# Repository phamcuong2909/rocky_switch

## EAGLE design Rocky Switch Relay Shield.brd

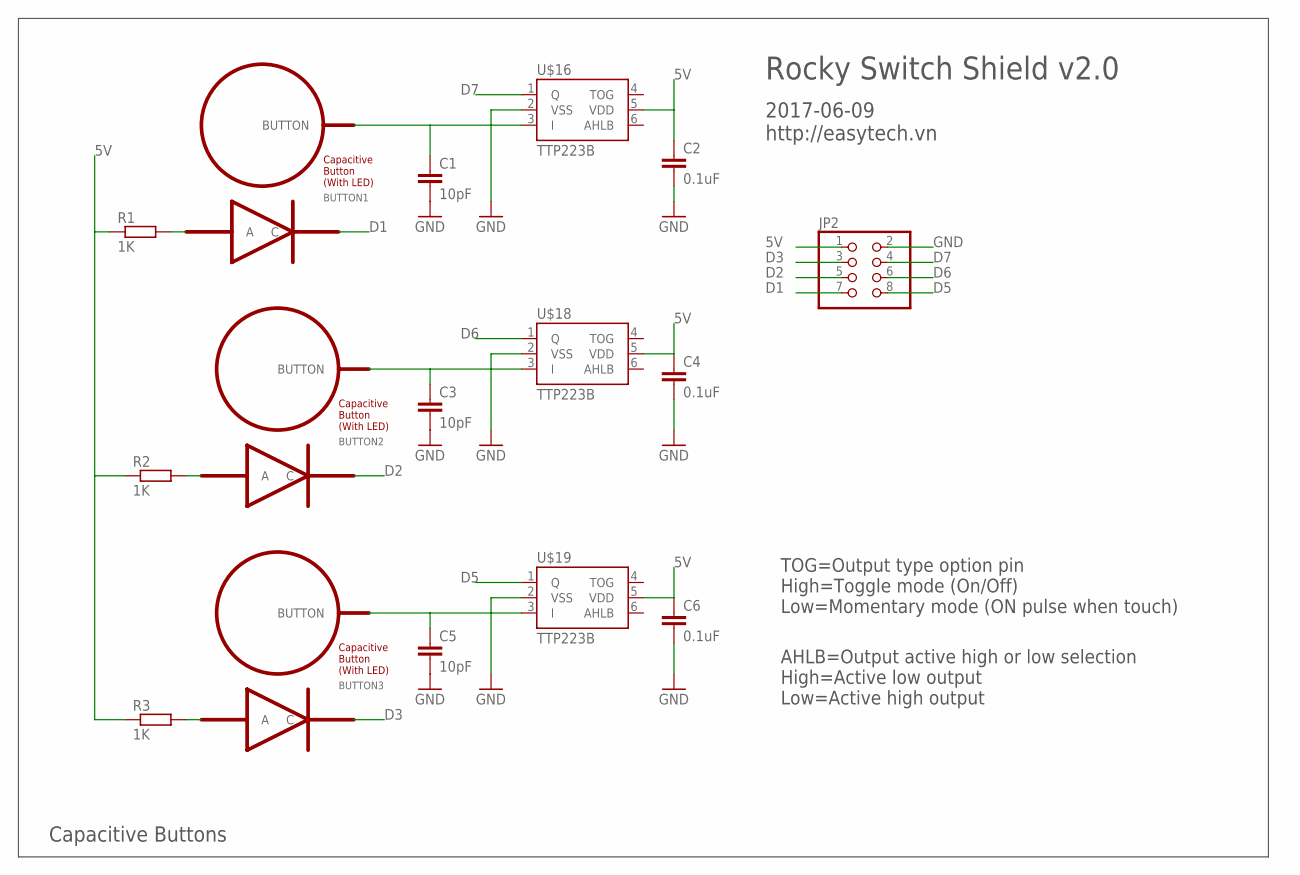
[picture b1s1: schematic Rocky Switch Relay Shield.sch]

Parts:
BUTTON1, BUTTON2, BUTTON3: BUTTON_PASSIVE_LED
C1, C3, C5: 10pF; C0805K
C2, C4, C6: 0.1uF; C0805K
JP2: PINHD-2X4; 2X04
R1, R2, R3: 1K; R0805
U$16, U$18, U$19: TTP223B; SOT23-6

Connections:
5V: C2.1, C4.1, C6.1, JP2.1, R1.1, R2.1, R3.1, U$16.5 (VDD), U$18.5 (VDD), U$19.5 (VDD)
D1: BUTTON1.C, JP2.7
D2: BUTTON2.C, JP2.5
D3: BUTTON3.C, JP2.3
D5: JP2.8, U$19.1 (Q)
D6: JP2.6, U$18.1 (Q)
D7: JP2.4, U$16.1 (Q)
GND: C1.2, C2.2, C3.2, C4.2, C5.2, C6.2, JP2.2, U$16.2 (VSS), U$18.2 (VSS), U$19.2 (VSS)
I1: BUTTON1.BUTTON, C1.1, U$16.3 (I)
I2: BUTTON2.BUTTON, C3.1, U$18.3 (I)
I3: BUTTON3.BUTTON, C5.1, U$19.3 (I)
unnamed: BUTTON1.A, R1.2
unnamed: BUTTON2.A, R2.2
unnamed: BUTTON3.A, R3.2

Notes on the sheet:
Rocky Switch Shield v2.0
2017-06-09 http://easytech.vn
Capacitive Buttons
TOG=Output type option pin High=Toggle mode (On/Off) Low=Momentary mode (ON pulse when touch)
AHLB=Output active high or low selection High=Active low output Low=Active high output

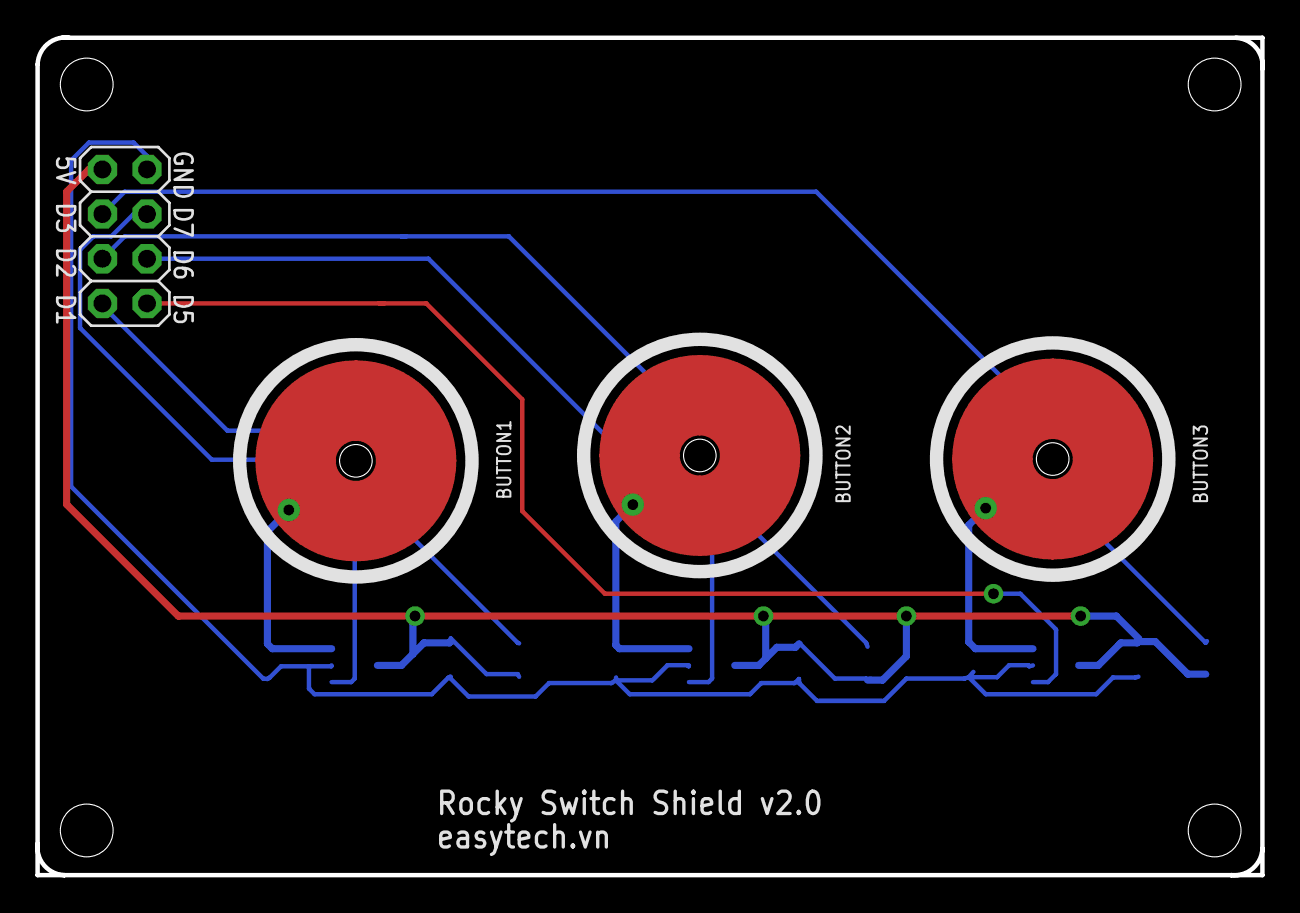
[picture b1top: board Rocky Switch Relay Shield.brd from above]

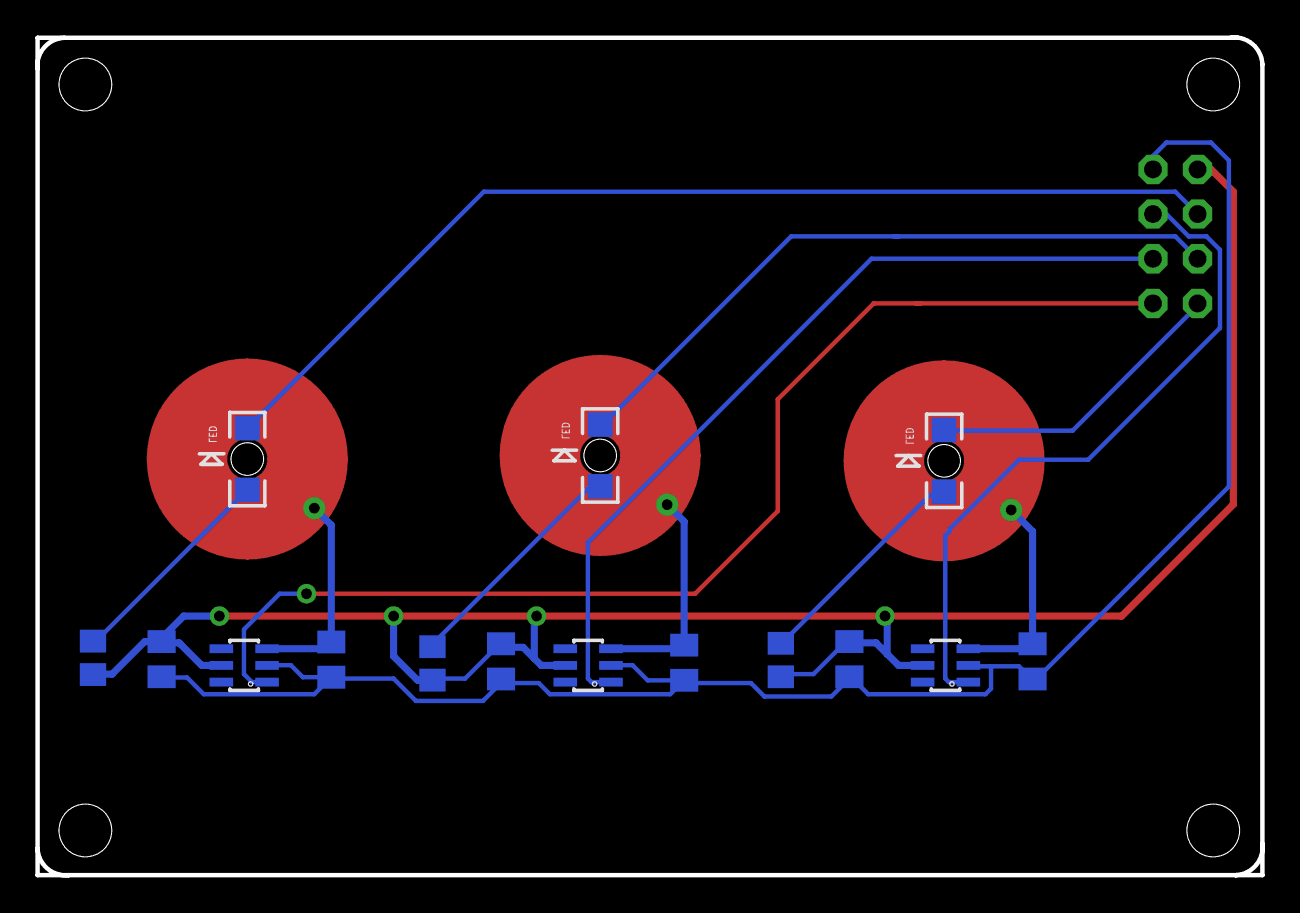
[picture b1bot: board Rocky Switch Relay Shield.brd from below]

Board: 2 copper layers, 69.7 x 47.6 mm, 20 parts (12 on the bottom side), 14 nets.

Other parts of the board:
U$6, U$7, U$8, U$9: KFH-M3

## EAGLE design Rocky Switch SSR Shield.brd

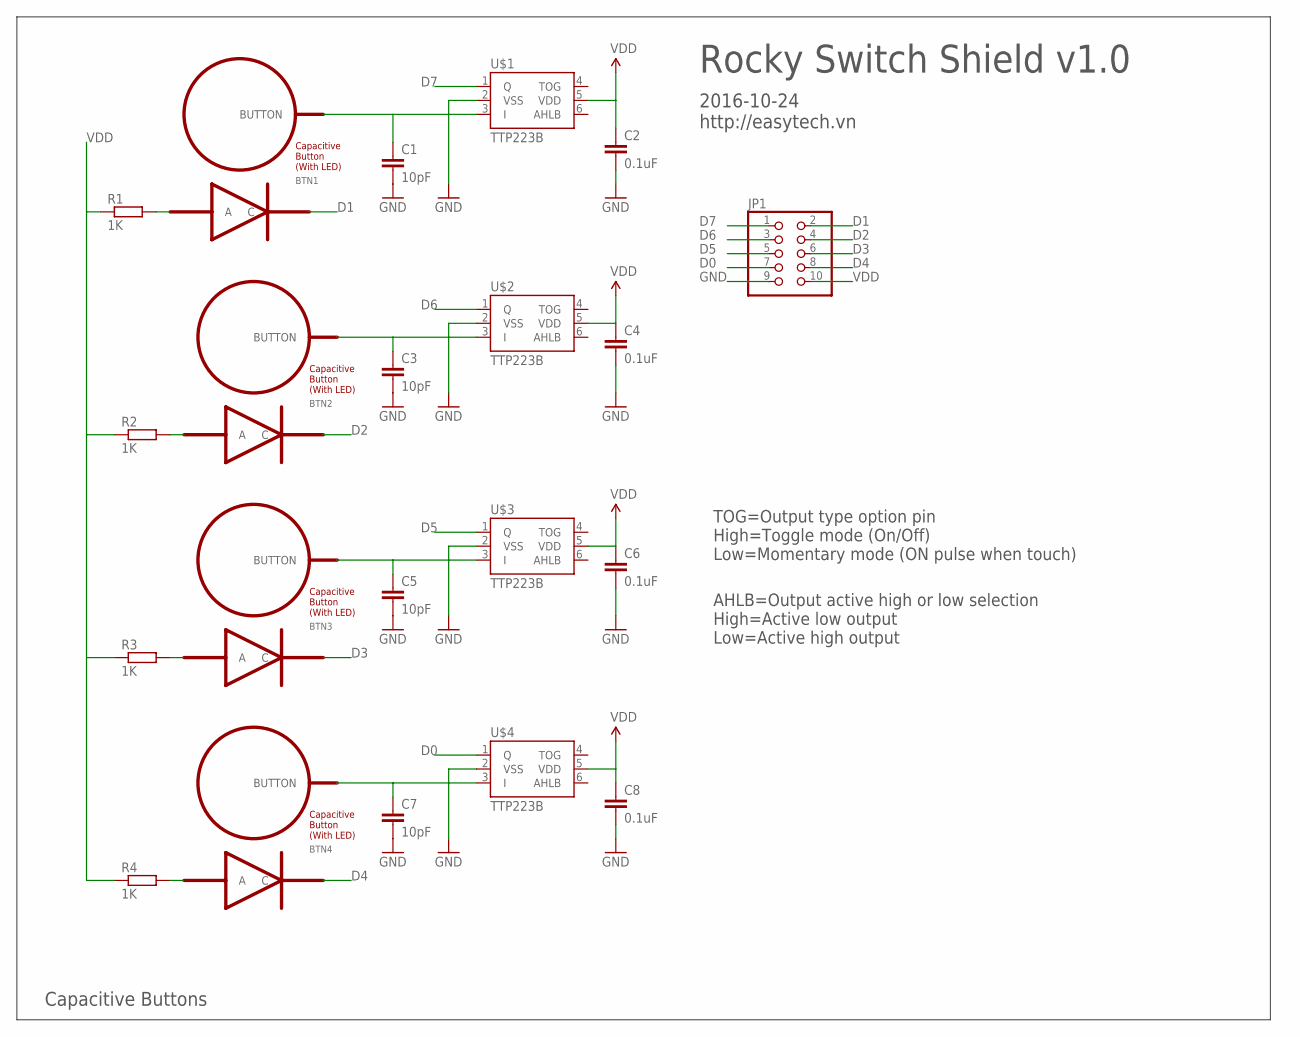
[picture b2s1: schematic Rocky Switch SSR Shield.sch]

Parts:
BTN1, BTN2, BTN3, BTN4: BUTTON_PASSIVE_LED
C1, C3, C5, C7: 10pF; C0805K
C2, C4, C6, C8: 0.1uF; C0805K
JP1: PINHD-2X5; 2X05
R1, R2, R3, R4: 1K; R0805
U$1, U$2, U$3, U$4: TTP223B; SOT23-6

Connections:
D0: JP1.7, U$4.1 (Q)
D1: BTN1.C, JP1.2
D2: BTN2.C, JP1.4
D3: BTN3.C, JP1.6
D4: BTN4.C, JP1.8
D5: JP1.5, U$3.1 (Q)
D6: JP1.3, U$2.1 (Q)
D7: JP1.1, U$1.1 (Q)
GND: C1.2, C2.2, C3.2, C4.2, C5.2, C6.2, C7.2, C8.2, JP1.9, U$1.2 (VSS), U$2.2 (VSS), U$3.2 (VSS), U$4.2 (VSS)
I1: BTN1.BUTTON, C1.1, U$1.3 (I)
I2: BTN2.BUTTON, C3.1, U$2.3 (I)
I3: BTN3.BUTTON, C5.1, U$3.3 (I)
I4: BTN4.BUTTON, C7.1, U$4.3 (I)
unnamed: BTN1.A, R1.2
unnamed: BTN2.A, R2.2
unnamed: BTN3.A, R3.2
unnamed: BTN4.A, R4.2
VDD: C2.1, C4.1, C6.1, C8.1, JP1.10, R1.1, R2.1, R3.1, R4.1, U$1.5 (VDD), U$2.5 (VDD), U$3.5 (VDD), U$4.5 (VDD)

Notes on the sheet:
Rocky Switch Shield v1.0
2016-10-24 http://easytech.vn
Capacitive Buttons
TOG=Output type option pin High=Toggle mode (On/Off) Low=Momentary mode (ON pulse when touch)
AHLB=Output active high or low selection High=Active low output Low=Active high output

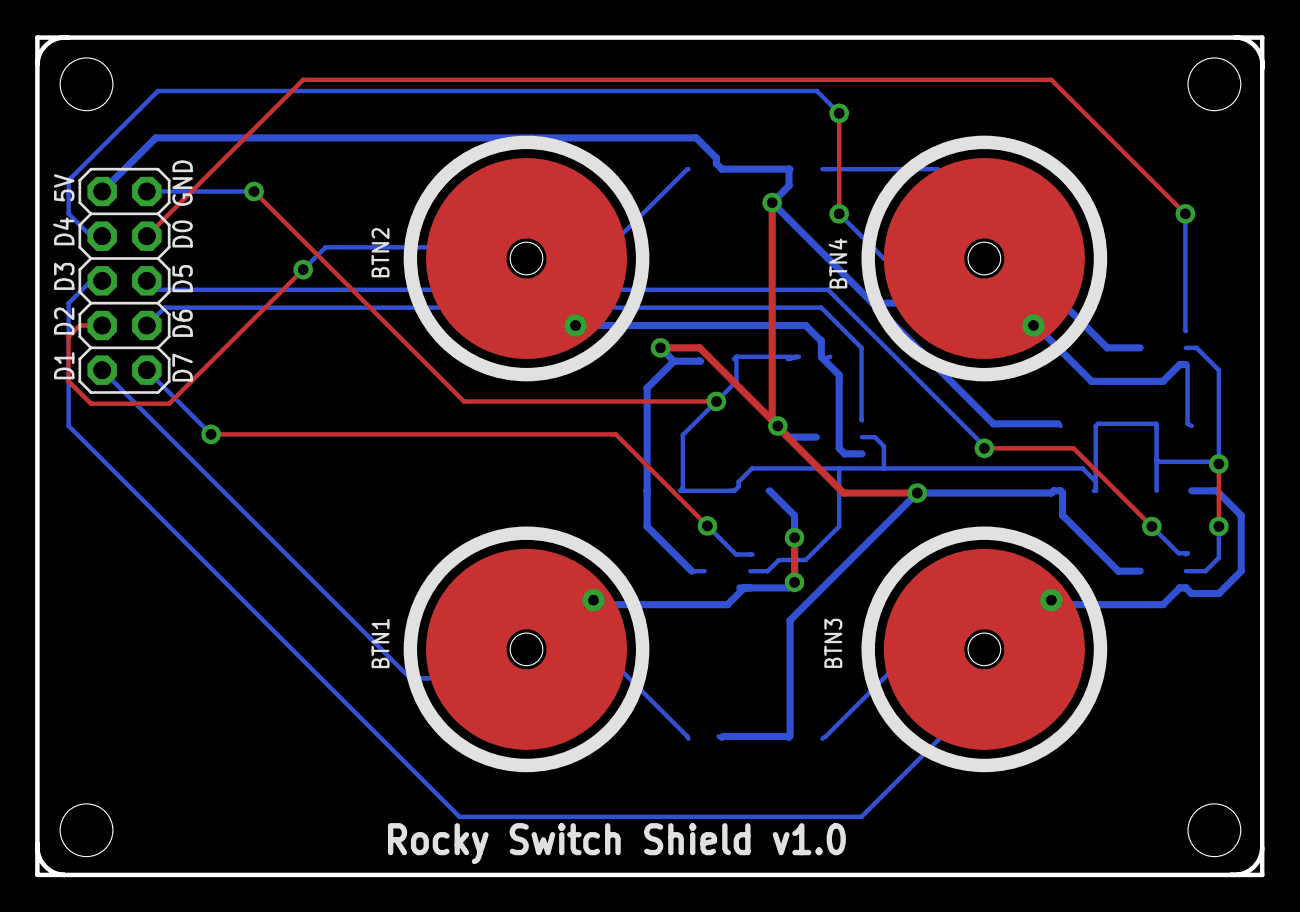
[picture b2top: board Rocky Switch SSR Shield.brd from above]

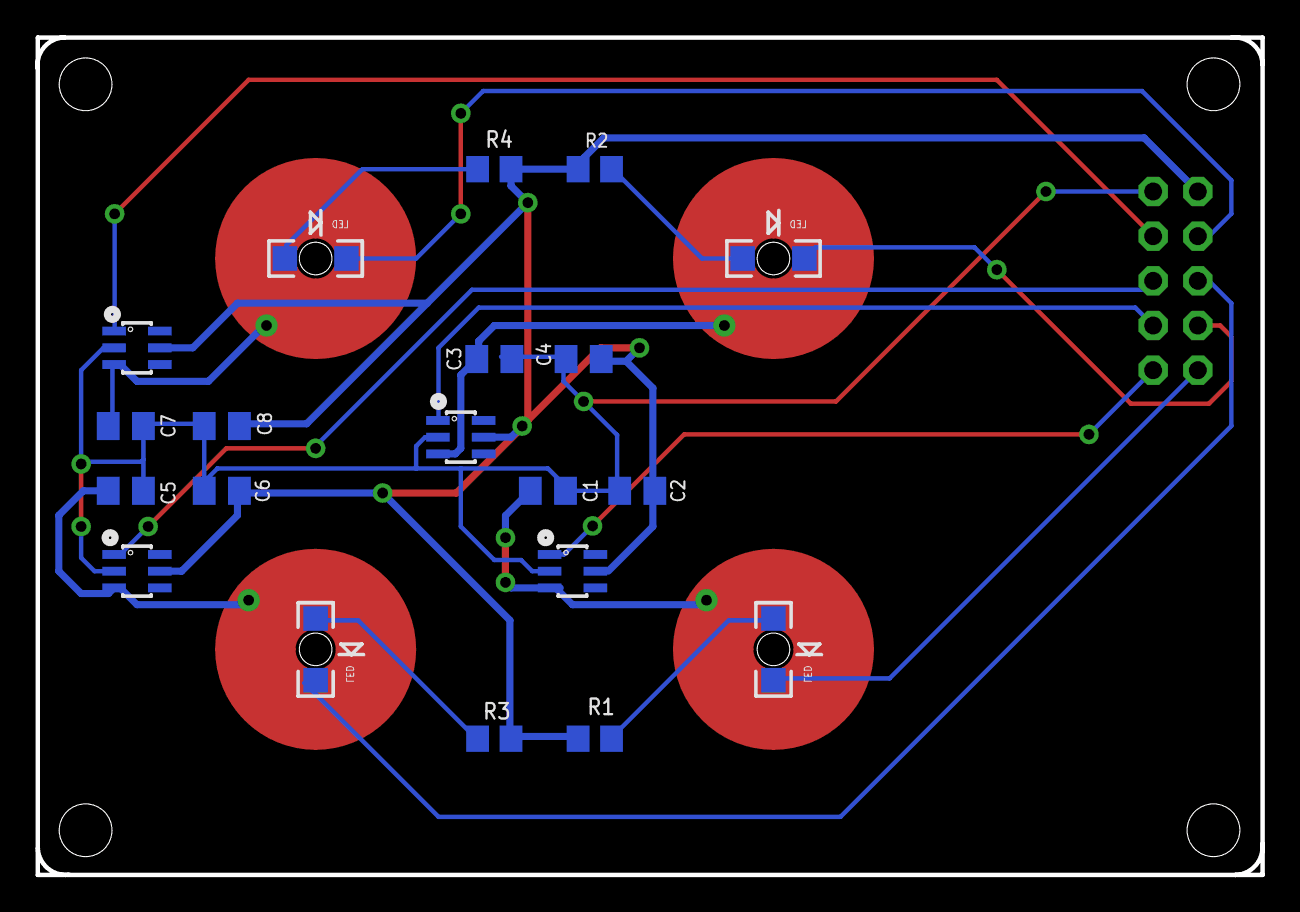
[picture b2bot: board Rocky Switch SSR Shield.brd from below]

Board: 2 copper layers, 69.7 x 47.6 mm, 25 parts (16 on the bottom side), 18 nets.

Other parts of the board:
U$6, U$7, U$8, U$9: KFH-M3

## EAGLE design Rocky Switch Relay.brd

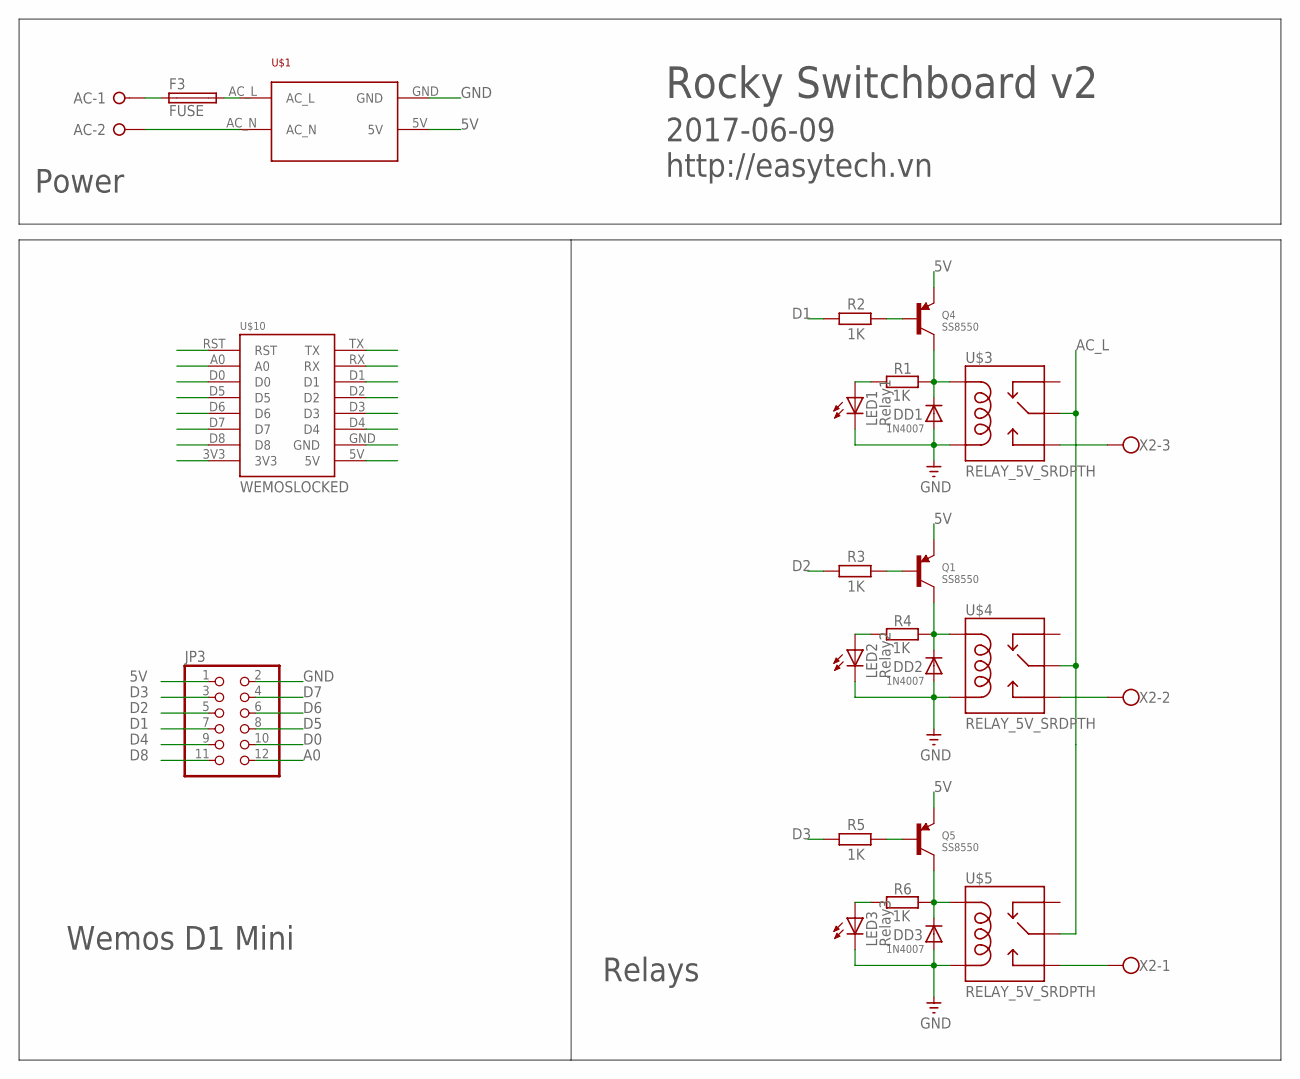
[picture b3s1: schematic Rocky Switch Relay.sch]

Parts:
AC: W237-02P; W237-132
DD1, DD2, DD3: 1N4007; SMADIODE
F3: FUSE; TE5
JP3: PINHD-2X6; 2X06
LED1: Relay1; CHIP-LED0805
LED2: Relay2; CHIP-LED0805
LED3: Relay3; CHIP-LED0805
Q1, Q4, Q5: SS8550; SOT23-W
R1, R2, R3, R4, R5, R6: 1K; R0805
U$1: POWER_SUPPLY_220VAC_5V
U$3, U$4, U$5: RELAY_5V_SRDPTH; SRD-05VDC-SL-C
U$10: WEMOSLOCKED; WEMOS_LOCKED
X2: W237-103

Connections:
3V3: U$10.3V3
5V: JP3.1, Q1.2 (E), Q4.2 (E), Q5.2 (E), U$1.5V, U$10.5V
A0: JP3.12, U$10.A0
AC_L: F3.2, U$1.AC_L, U$3.SWCOMMON, U$4.SWCOMMON, U$5.SWCOMMON
AC_N: AC.2, U$1.AC_N
D0: JP3.10, U$10.D0
D1: JP3.7, R2.1, U$10.D1
D2: JP3.5, R3.1, U$10.D2
D3: JP3.3, R5.1, U$10.D3
D4: JP3.9, U$10.D4
D5: JP3.8, U$10.D5
D6: JP3.6, U$10.D6
D7: JP3.4, U$10.D7
D8: JP3.11, U$10.D8
GND: DD1.A, DD2.A, DD3.A, JP3.2, LED1.C, LED2.C, LED3.C, U$1.GND, U$3.COIL0, U$4.COIL0, U$5.COIL0, U$10.GND
unnamed: DD2.C, Q1.3 (C), R4.1, U$4.COIL1
unnamed: U$3.SWOPEN, X2.3
unnamed: LED1.A, R1.2
unnamed: DD3.C, Q5.3 (C), R6.1, U$5.COIL1
unnamed: Q1.1 (B), R3.2
unnamed: Q4.1 (B), R2.2
unnamed: LED2.A, R4.2
unnamed: U$4.SWOPEN, X2.2
unnamed: Q5.1 (B), R5.2
unnamed: LED3.A, R6.2
unnamed: U$5.SWOPEN, X2.1
unnamed: AC.1, F3.1
unnamed: DD1.C, Q4.3 (C), R1.1, U$3.COIL1
RST1: U$10.RST
RX: U$10.RX
TX: U$10.TX

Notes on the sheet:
Rocky Switchboard v2
2017-06-09 http://easytech.vn
Power
Wemos D1 Mini
Relays

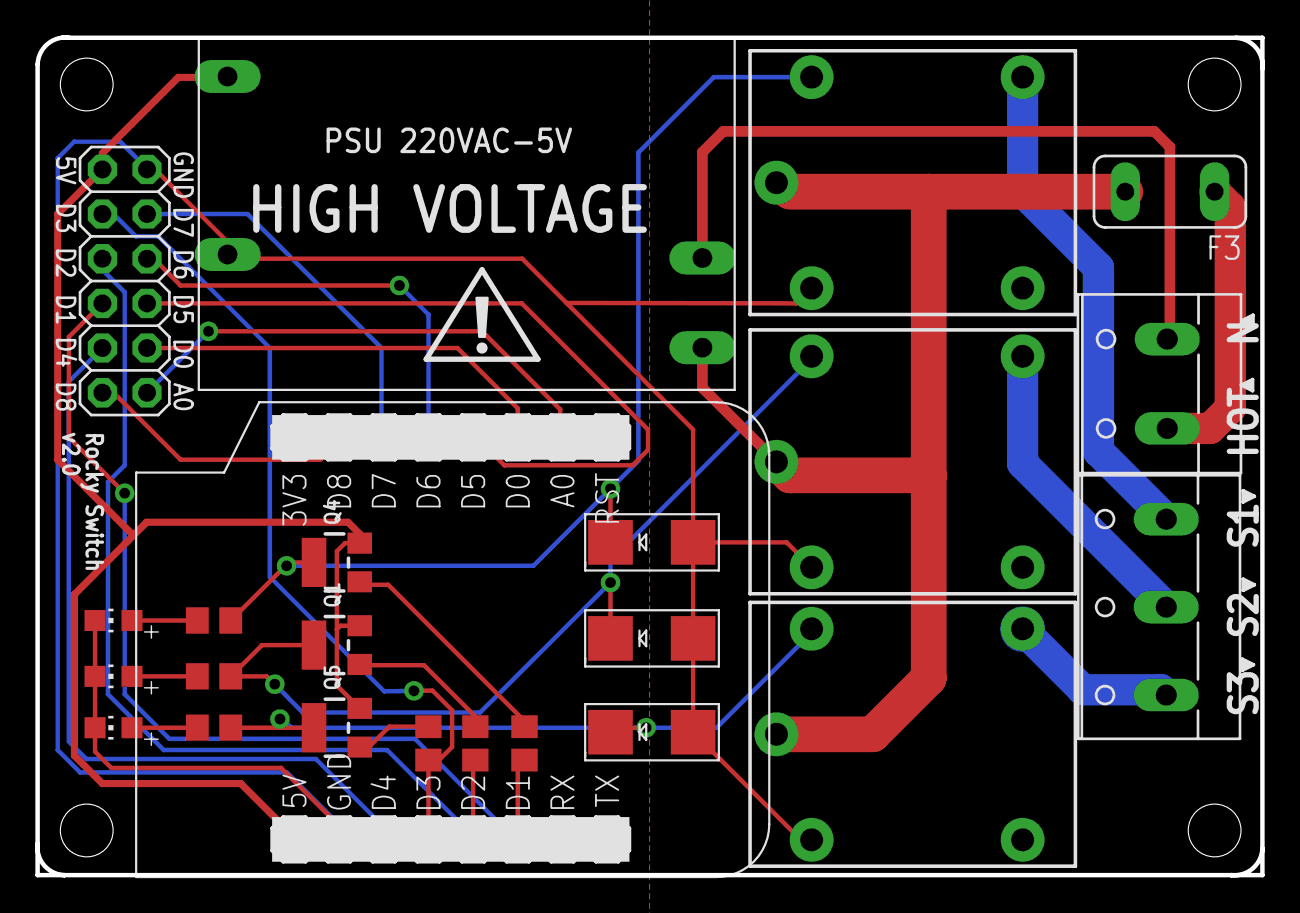
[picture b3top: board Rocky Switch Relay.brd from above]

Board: 2 copper layers, 69.7 x 47.6 mm, 35 parts (1 on the bottom side), 27 nets.

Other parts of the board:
U$2, U$17: ICON_EXL-S
U$6, U$7, U$8, U$9: KFH-M3
U$11, U$12, U$13, U$14, U$15: ICON_PIN1_B

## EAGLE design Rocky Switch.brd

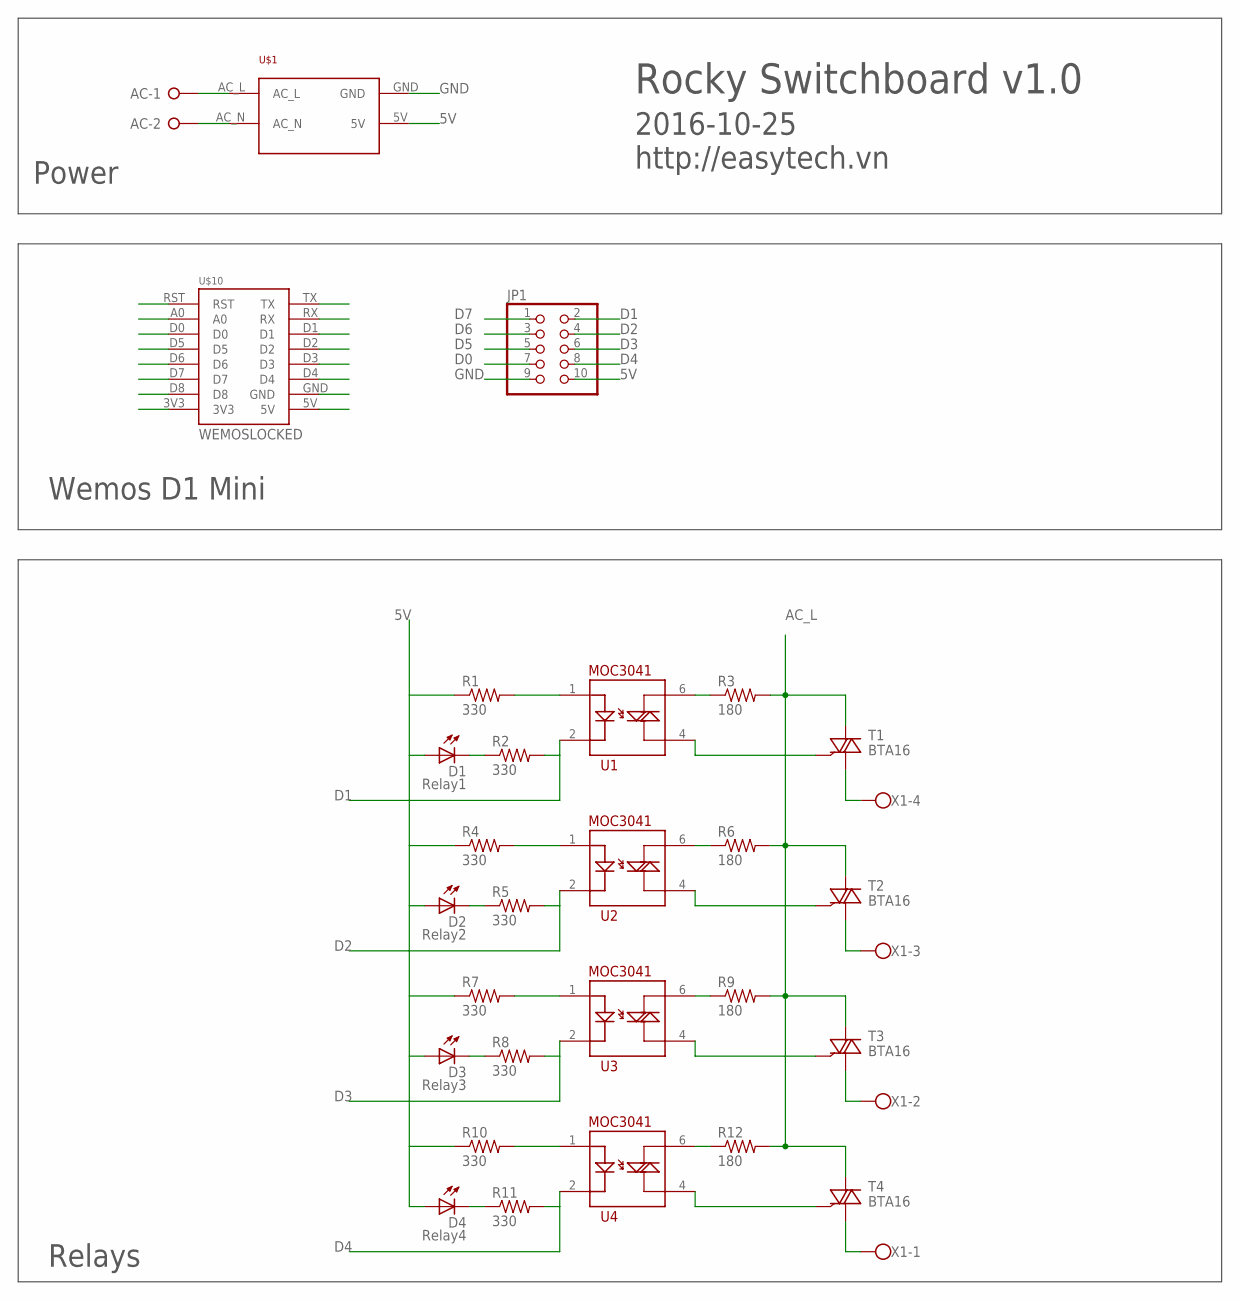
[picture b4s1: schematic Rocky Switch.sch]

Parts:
AC: W237-02P; W237-132
D1: Relay1; CHIP-LED0805
D2: Relay2; CHIP-LED0805
D3: Relay3; CHIP-LED0805
D4: Relay4; CHIP-LED0805
JP1: PINHD-2X5; 2X05
R1, R2, R4, R5, R7, R8, R10, R11: 330; R0805
R3, R6, R9, R12: 180; 0204/7
T1, T2, T3, T4: BTA16; TO220BV
U1, U2, U3, U4: MOC3041; DIL06
U$1: POWER_SUPPLY_220VAC_5V
U$10: WEMOSLOCKED; WEMOS_LOCKED
X1: W237-4

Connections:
3V3: U$10.3V3
5V: D1.A, D2.A, D3.A, D4.A, JP1.10, R1.1, R4.1, R7.1, R10.1, U$1.5V, U$10.5V
A0: U$10.A0
AC_L: AC.1, R3.2, R6.2, R9.2, R12.2, T1.T2 (A2), T2.T2 (A2), T3.T2 (A2), T4.T2 (A2), U$1.AC_L
AC_N: AC.2, U$1.AC_N
D0: JP1.7, U$10.D0
D1: JP1.2, R2.2, U1.2, U$10.D1
D2: JP1.4, R5.2, U2.2, U$10.D2
D3: JP1.6, R8.2, U3.2, U$10.D3
D4: JP1.8, R11.2, U4.2, U$10.D4
D5: JP1.5, U$10.D5
D6: JP1.3, U$10.D6
D7: JP1.1, U$10.D7
D8: U$10.D8
GND: JP1.9, U$1.GND, U$10.GND
unnamed: T1.G, U1.4
unnamed: R1.2, U1.1
unnamed: R3.1, U1.6
unnamed: T2.G, U2.4
unnamed: R4.2, U2.1
unnamed: R6.1, U2.6
unnamed: T3.G, U3.4
unnamed: R7.2, U3.1
unnamed: R9.1, U3.6
unnamed: T3.T1 (A1), X1.2
unnamed: T2.T1 (A1), X1.3
unnamed: T1.T1 (A1), X1.4
unnamed: D1.C, R2.1
unnamed: D2.C, R5.1
unnamed: D3.C, R8.1
unnamed: T4.G, U4.4
unnamed: R10.2, U4.1
unnamed: R12.1, U4.6
unnamed: T4.T1 (A1), X1.1
unnamed: D4.C, R11.1
RST1: U$10.RST
RX: U$10.RX
TX: U$10.TX

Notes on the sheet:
Rocky Switchboard v1.0
2016-10-25 http://easytech.vn
Power
Wemos D1 Mini
Relays

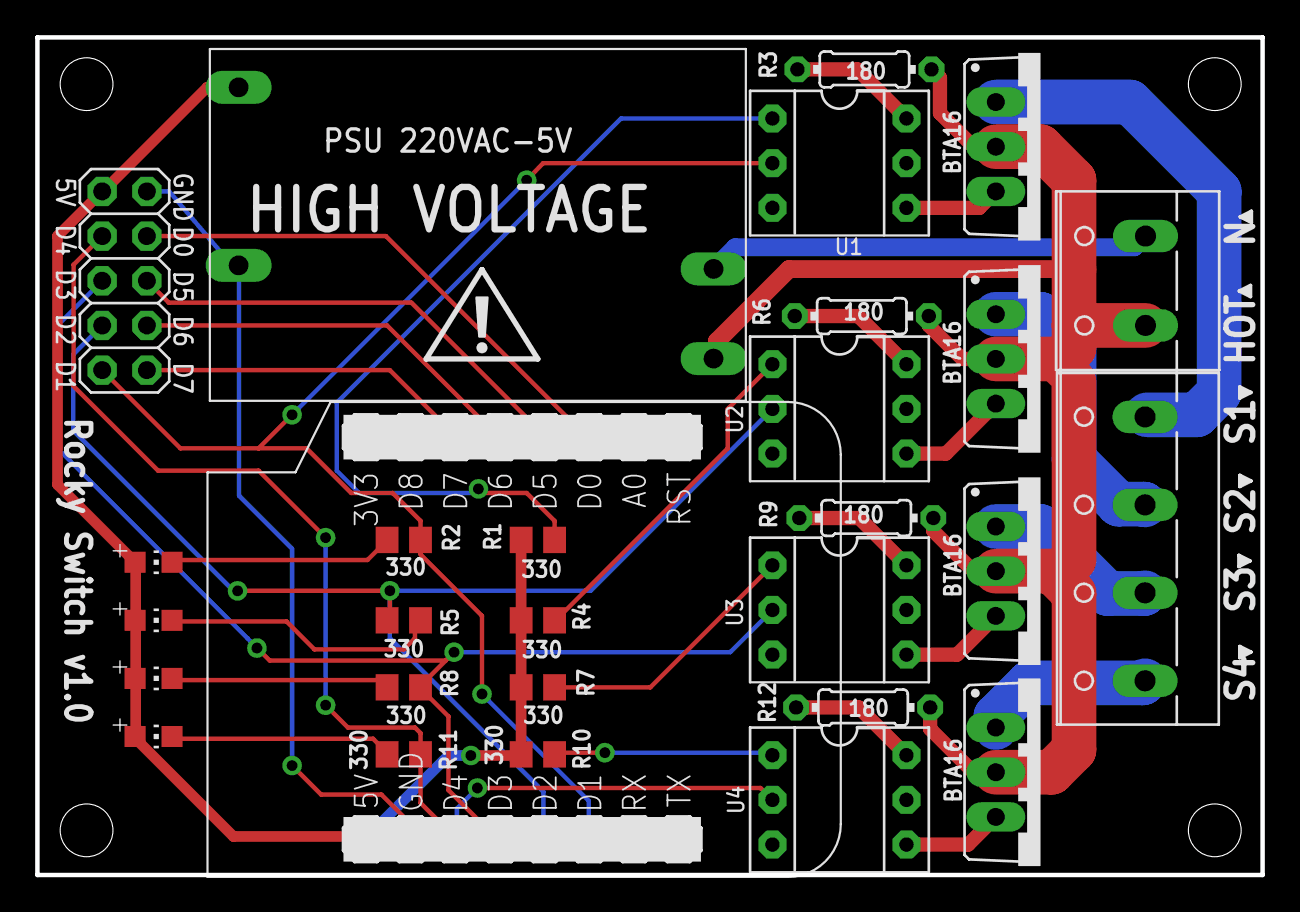
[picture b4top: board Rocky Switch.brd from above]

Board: 2 copper layers, 69.6 x 47.6 mm, 40 parts (0 on the bottom side), 32 nets.

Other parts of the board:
U$2, U$11, U$12, U$13, U$14, U$15: ICON_PIN1_B
U$6, U$7, U$8, U$9: KFH-M3
U$17: ICON_EXL-S

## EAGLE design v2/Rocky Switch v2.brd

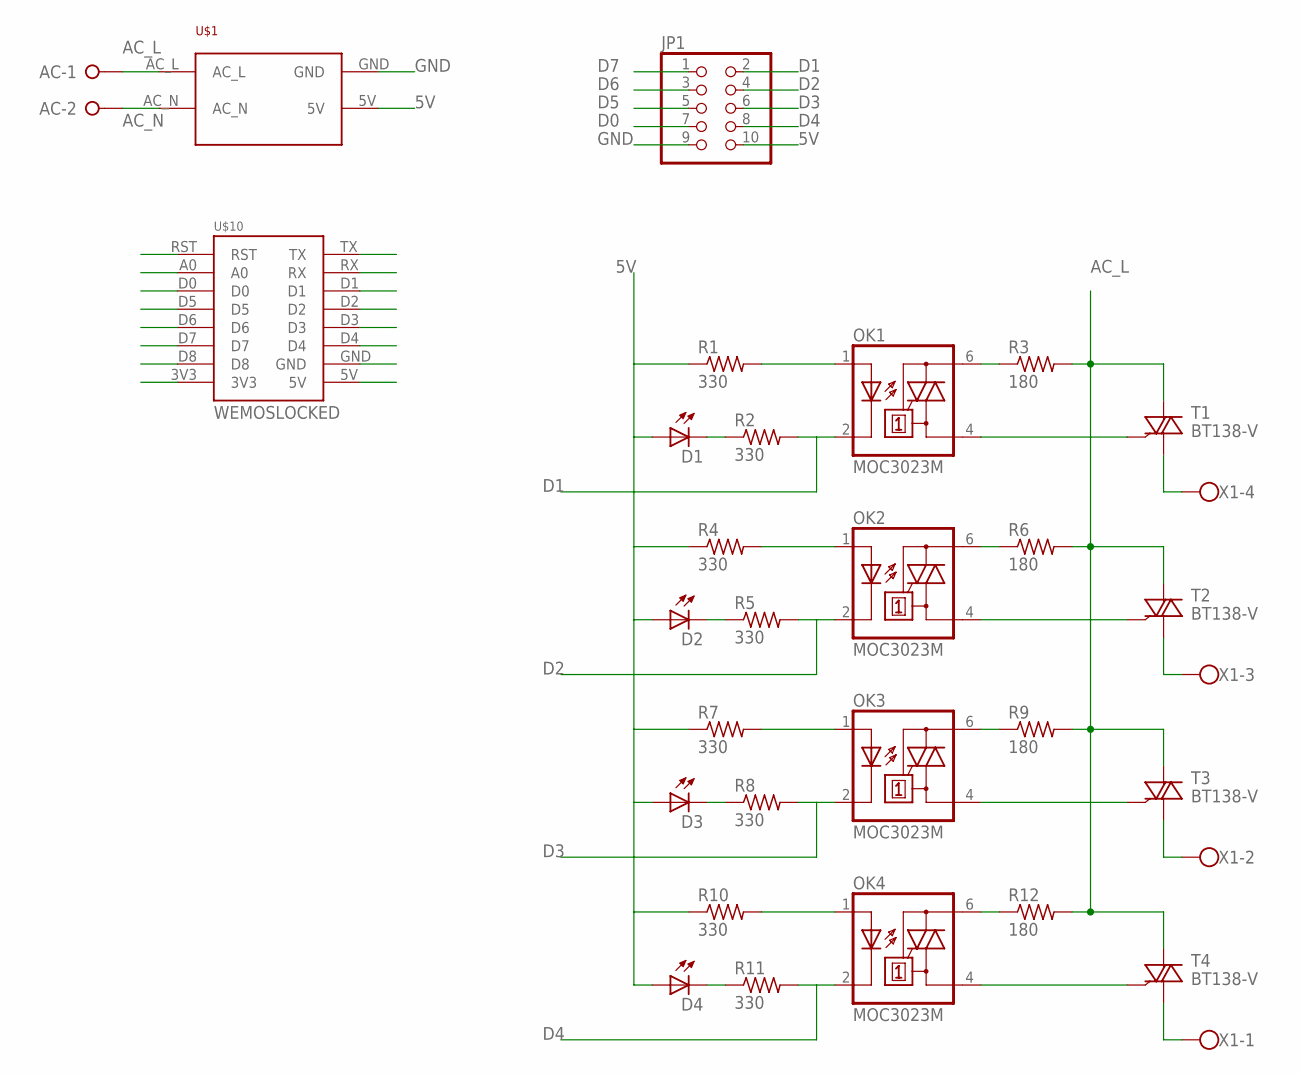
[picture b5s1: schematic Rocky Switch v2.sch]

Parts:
AC: W237-02P; W237-132
D1, D2, D3, D4: LED3MM
JP1: PINHD-2X5; 2X05
OK1, OK2, OK3, OK4: MOC3023M; DIL06
R1, R2, R4, R5, R7, R8, R10, R11: 330; 0204/7
R3, R6, R9, R12: 180; 0204/7
T1, T2, T3, T4: BT138-V; TO220BV
U$1: POWER_SUPPLY_220VAC_5V
U$10: WEMOSLOCKED; WEMOS_LOCKED
X1: W237-4

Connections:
3V3: U$10.3V3
5V: D1.A, D2.A, D3.A, D4.A, JP1.10, R1.1, R4.1, R7.1, R10.1, U$1.5V, U$10.5V
A0: U$10.A0
AC_L: AC.1, R3.2, R6.2, R9.2, R12.2, T1.T2 (A2), T2.T2 (A2), T3.T2 (A2), T4.T2 (A2), U$1.AC_L
AC_N: AC.2, U$1.AC_N
D0: JP1.7, U$10.D0
D1: JP1.2, OK1.2 (C), R2.2, U$10.D1
D2: JP1.4, OK2.2 (C), R5.2, U$10.D2
D3: JP1.6, OK3.2 (C), R8.2, U$10.D3
D4: JP1.8, OK4.2 (C), R11.2, U$10.D4
D5: JP1.5, U$10.D5
D6: JP1.3, U$10.D6
D7: JP1.1, U$10.D7
D8: U$10.D8
GND: JP1.9, U$1.GND, U$10.GND
unnamed: OK1.4 (A1), T1.G
unnamed: OK1.1 (A), R1.2
unnamed: OK1.6 (A2), R3.1
unnamed: OK2.4 (A1), T2.G
unnamed: OK2.1 (A), R4.2
unnamed: OK2.6 (A2), R6.1
unnamed: OK3.4 (A1), T3.G
unnamed: OK3.1 (A), R7.2
unnamed: OK3.6 (A2), R9.1
unnamed: T3.T1 (A1), X1.2
unnamed: T2.T1 (A1), X1.3
unnamed: T1.T1 (A1), X1.4
unnamed: D1.K (C), R2.1
unnamed: D2.K (C), R5.1
unnamed: D3.K (C), R8.1
unnamed: OK4.4 (A1), T4.G
unnamed: OK4.1 (A), R10.2
unnamed: OK4.6 (A2), R12.1
unnamed: T4.T1 (A1), X1.1
unnamed: D4.K (C), R11.1
RST1: U$10.RST
RX: U$10.RX
TX: U$10.TX

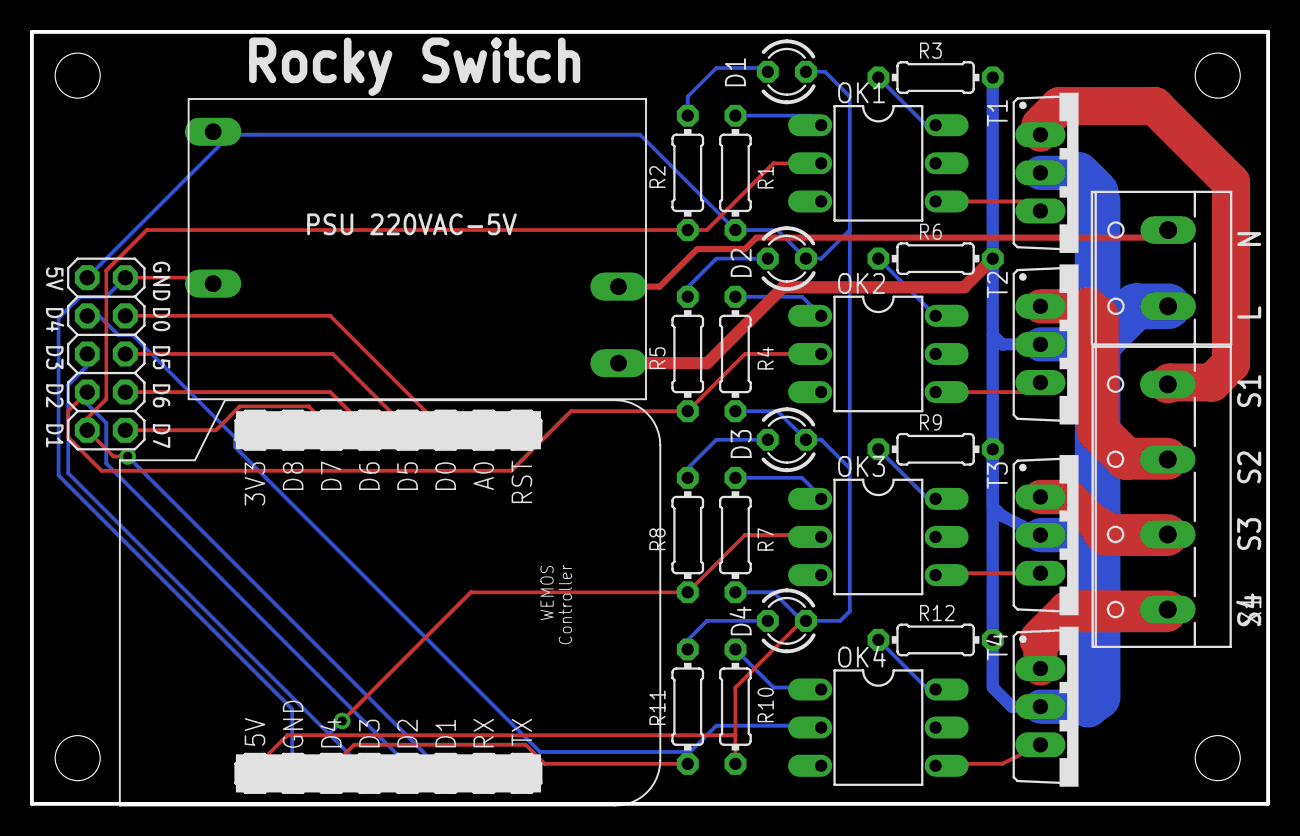
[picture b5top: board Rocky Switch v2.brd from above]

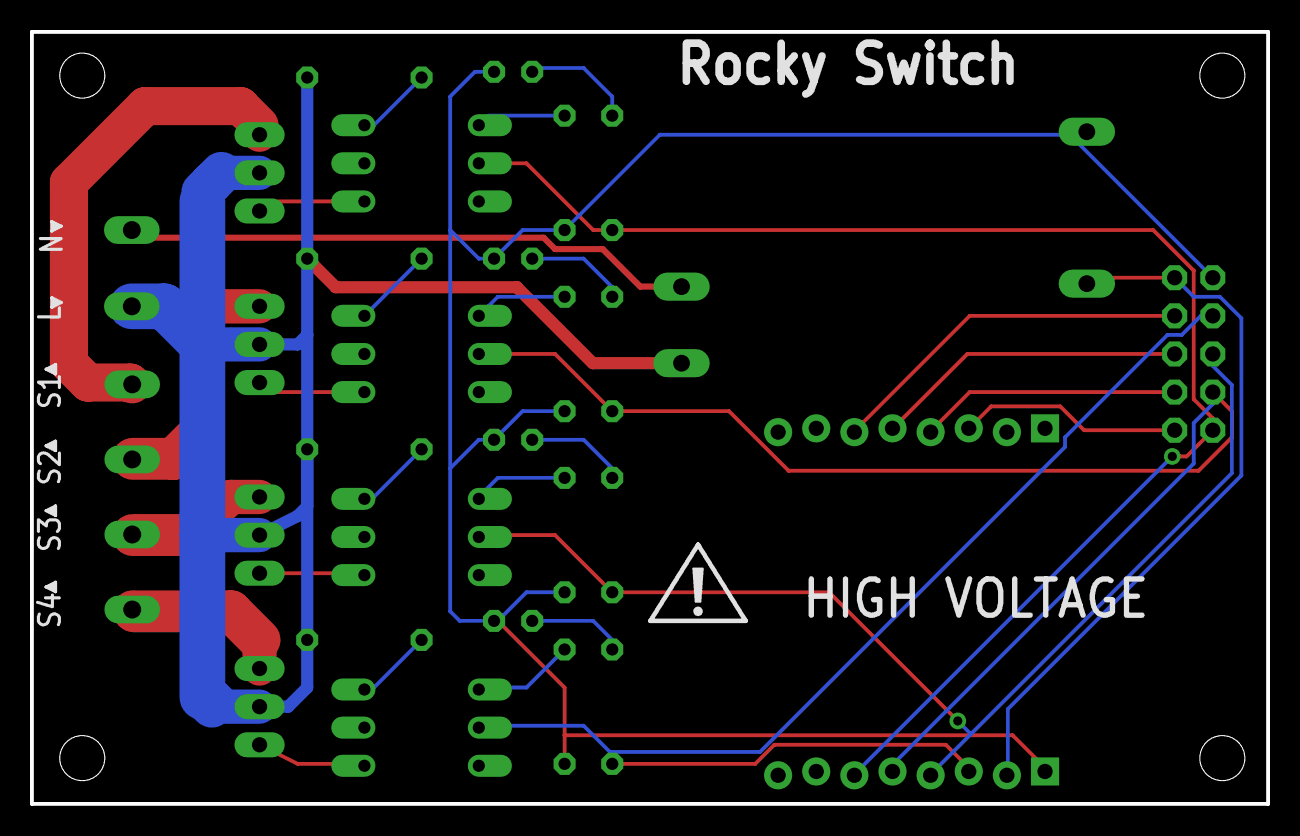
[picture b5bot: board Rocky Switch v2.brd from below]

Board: 2 copper layers, 82.3 x 51.4 mm, 40 parts (7 on the bottom side), 32 nets.

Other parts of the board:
U$2, U$11, U$12, U$13, U$14, U$15: ICON_PIN1_B
U$6, U$7, U$8, U$9: KFH-M3
U$17: ICON_EXL-S

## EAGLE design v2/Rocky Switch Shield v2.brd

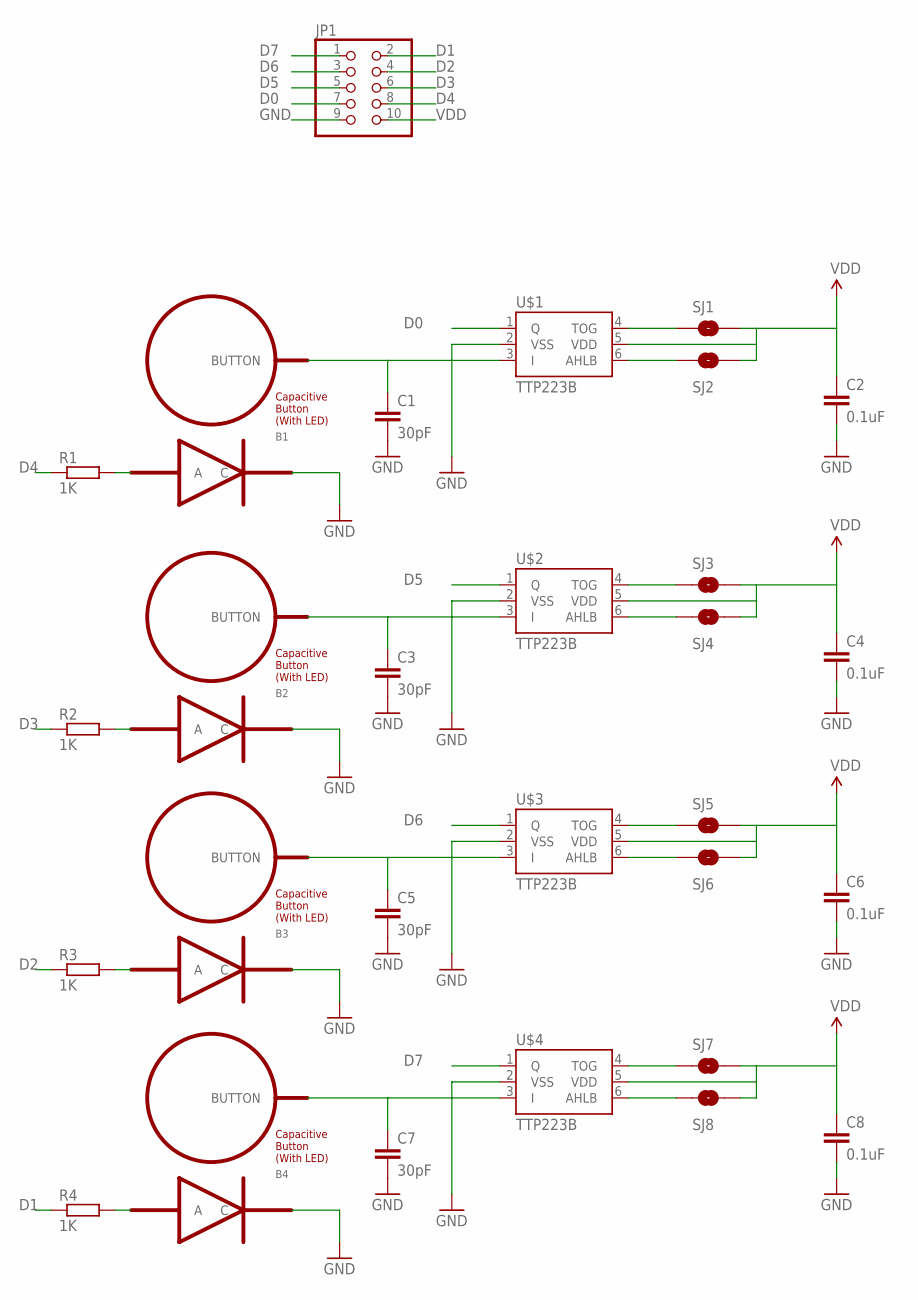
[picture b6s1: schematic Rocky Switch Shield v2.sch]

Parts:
B1, B2, B3, B4: BUTTON_PASSIVE_LED; BUTTON_PASSIVE_12MM_LED
C1, C3, C5, C7: 30pF; C0805K
C2, C4, C6, C8: 0.1uF; C0805K
JP1: PINHD-2X5; 2X05
R1, R2, R3, R4: 1K; R0805
SJ1, SJ2, SJ3, SJ4, SJ5, SJ6, SJ7, SJ8: JUMPER-PAD-2-NOYES_SILK; PAD-JUMPER-2-NO_YES_SILK
U$1, U$2, U$3, U$4: TTP223B; SOT23-6

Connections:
D0: JP1.7, U$1.1 (Q)
D1: JP1.2, R4.1
D2: JP1.4, R3.1
D3: JP1.6, R2.1
D4: JP1.8, R1.1
D5: JP1.5, U$2.1 (Q)
D6: JP1.3, U$3.1 (Q)
D7: JP1.1, U$4.1 (Q)
GND: B1.C, B2.C, B3.C, B4.C, C1.2, C2.2, C3.2, C4.2, C5.2, C6.2, C7.2, C8.2, JP1.9, U$1.2 (VSS), U$2.2 (VSS), U$3.2 (VSS), U$4.2 (VSS)
I1: B1.BUTTON, C1.1, U$1.3 (I)
I2: B2.BUTTON, C3.1, U$2.3 (I)
I3: B3.BUTTON, C5.1, U$3.3 (I)
I4: B4.BUTTON, C7.1, U$4.3 (I)
unnamed: SJ1.1, U$1.4 (TOG)
unnamed: B1.A, R1.2
unnamed: SJ2.1, U$1.6 (AHLB)
unnamed: SJ3.1, U$2.4 (TOG)
unnamed: SJ4.1, U$2.6 (AHLB)
unnamed: B2.A, R2.2
unnamed: SJ5.1, U$3.4 (TOG)
unnamed: SJ6.1, U$3.6 (AHLB)
unnamed: B3.A, R3.2
unnamed: SJ7.1, U$4.4 (TOG)
unnamed: SJ8.1, U$4.6 (AHLB)
unnamed: B4.A, R4.2
VDD: C2.1, C4.1, C6.1, C8.1, JP1.10, SJ1.2, SJ2.2, SJ3.2, SJ4.2, SJ5.2, SJ6.2, SJ7.2, SJ8.2, U$1.5 (VDD), U$2.5 (VDD), U$3.5 (VDD), U$4.5 (VDD)

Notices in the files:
parts and their libraries:
penn-engineering: Copyright (C) 2010, Bob Starr
SparkFun: Licensing: CC v3.0 Share-Alike You are welcome to use this library for commercial purposes.
dicons: Copyright (C) 2008, Bob Starr
PatternAgents-TouchWidgets: License : http://creativecommons.org/licenses/by-sa/4.0/ (Creative Commons 4.0)
